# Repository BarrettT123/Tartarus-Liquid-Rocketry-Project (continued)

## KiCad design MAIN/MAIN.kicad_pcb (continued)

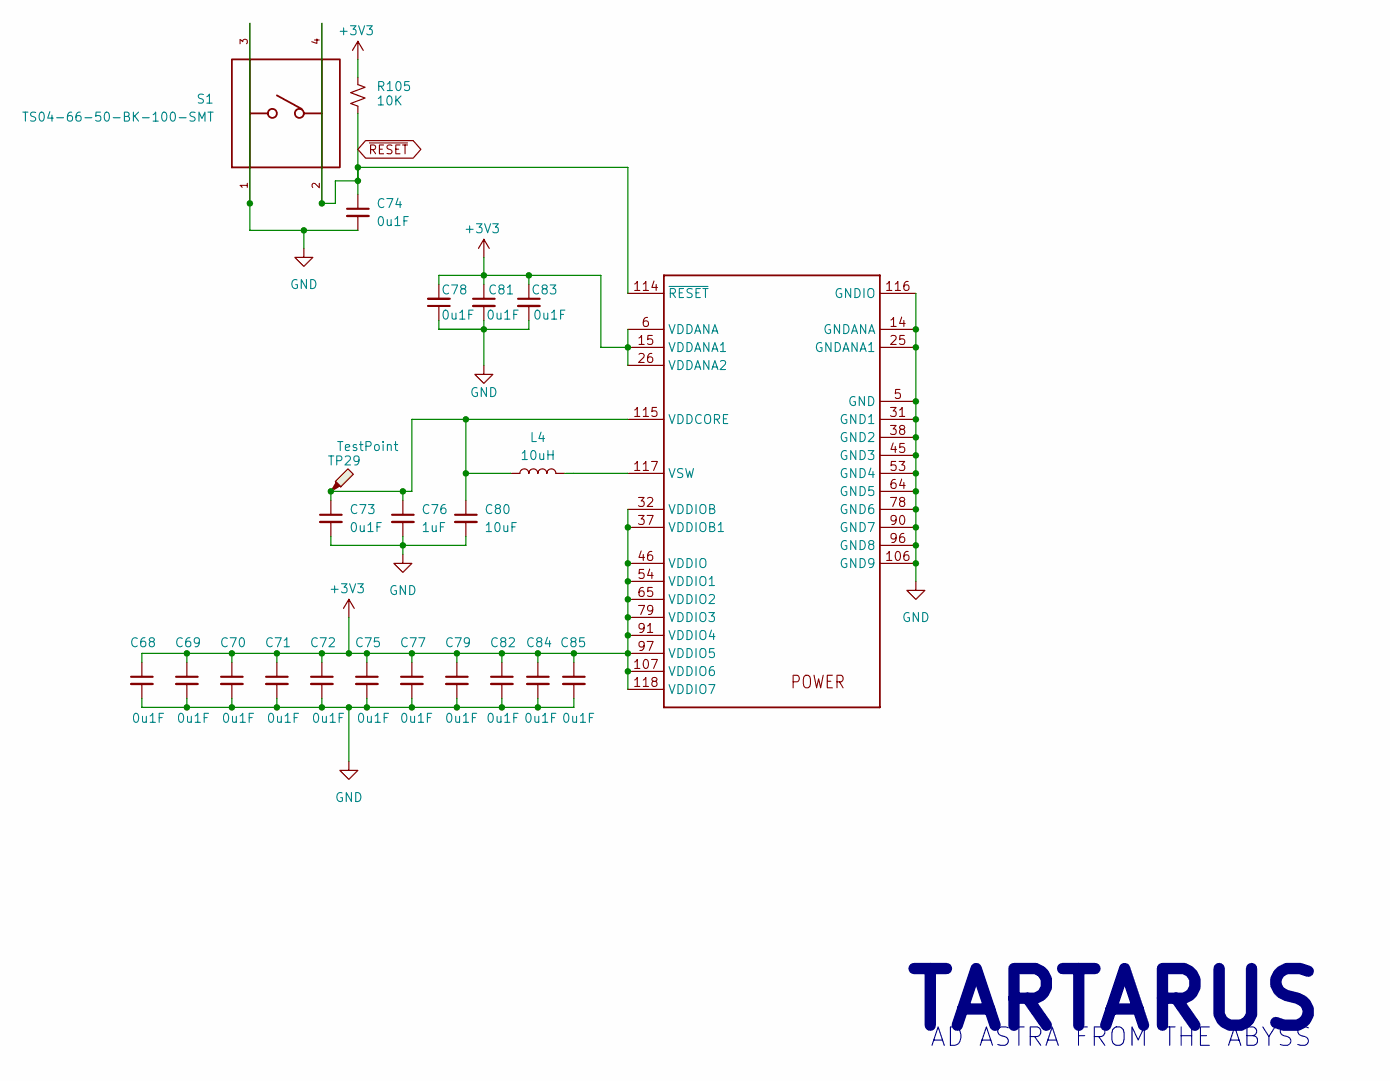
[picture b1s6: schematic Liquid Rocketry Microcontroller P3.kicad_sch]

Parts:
C68, C69, C70, C71, C72, C73, C74, C75, C77, C78, C79, C81, C82, C83, C84, C85: 0u1F; C_0603_1608Metric
C76: 1uF; C_0603_1608Metric
C80: 10uF; C_0603_1608Metric
L4: 10uH; L_1008_2520Metric
R105: 10K; R_0603_1608Metric
S1: TS04-66-50-BK-100-SMT; SW_TS04-66-50-BK-100-SMT; PARTREV 1.0
TP29: TestPoint; TestPoint_Pad_D1.0mm
U$1: SAMD51PXXA; SAMD51P20A-AF

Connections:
+3V3: C68.1, C69.1, C70.1, C71.1, C72.1, C75.1, C77.1, C78.2, C79.1, C81.1, C82.1, C83.1, C84.1, C85.1, R105.1, U$1.6 (VDDANA), U$1.15 (VDDANA1), U$1.26 (VDDANA2), U$1.32 (VDDIOB), U$1.37 (VDDIOB1), U$1.46 (VDDIO), U$1.54 (VDDIO1), U$1.65 (VDDIO2), U$1.79 (VDDIO3), U$1.91 (VDDIO4), U$1.97 (VDDIO5), U$1.107 (VDDIO6), U$1.118 (VDDIO7); also elsewhere on the board
GND: C68.2, C69.2, C70.2, C71.2, C72.2, C73.2, C74.2, C75.2, C76.2, C77.2, C78.1, C79.2, C80.2, C81.2, C82.2, C83.2, C84.2, C85.2, S1.1, S1.3, U$1.5 (GND), U$1.14 (GNDANA), U$1.25 (GNDANA1), U$1.31 (GND1), U$1.38 (GND2), U$1.45 (GND3), U$1.53 (GND4), U$1.64 (GND5), U$1.78 (GND6), U$1.90 (GND7), U$1.96 (GND8), U$1.106 (GND9), U$1.116 (GNDIO); also elsewhere on the board
unnamed: C73.1, C76.1, C80.1, L4.1, TP29.1, U$1.115 (VDDCORE)
unnamed: L4.2, U$1.117 (VSW)
~RESET: C74.1, R105.2, S1.2, S1.4, U$1.114 (~RESET); also elsewhere on the board

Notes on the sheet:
AD ASTRA FROM THE ABYSS
TARTARUS

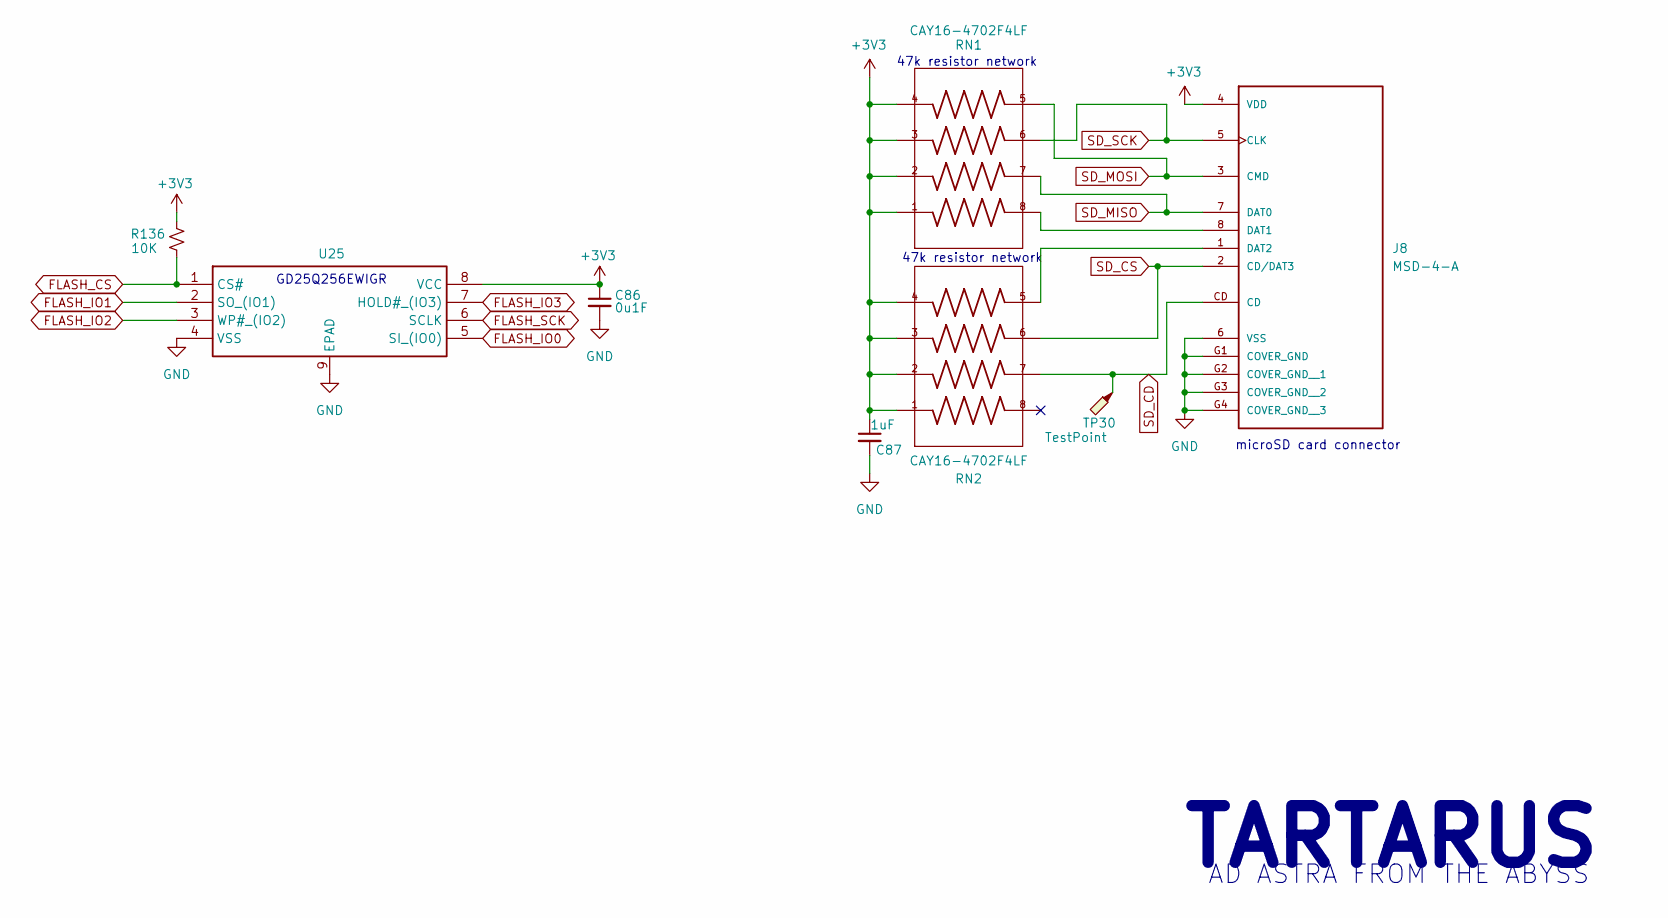
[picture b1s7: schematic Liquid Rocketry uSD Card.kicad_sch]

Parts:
C86: 0u1F; C_0603_1608Metric
C87: 1uF; C_0603_1608Metric
J8: MSD-4-A; CUI_MSD-4-A
R136: 10K; R_0603_1608Metric
RN1, RN2: CAY16-4702F4LF; CAY16_4702F4LF
TP30: TestPoint; TestPoint_Pad_D1.0mm
U25: GD25Q64ETIGR; WSON-8-1EP_6x5mm_P1.27mm_EP3.4x4mm; Mouser Part Number 363-GD25Q64ETIGR

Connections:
+3V3: C86.1, C87.1, J8.4 (VDD), R136.2, RN1.1, RN1.2, RN1.3, RN1.4, RN2.1, RN2.2, RN2.3, RN2.4, U25.8 (VCC); also elsewhere on the board
FLASH_CS: R136.1, U25.1 (CS#); also elsewhere on the board
FLASH_IO0: U25.5 (SI_(IO0)); also elsewhere on the board
FLASH_IO1: U25.2 (SO_(IO1)); also elsewhere on the board
FLASH_IO2: U25.3 (WP#_(IO2)); also elsewhere on the board
FLASH_IO3: U25.7 (HOLD#_(IO3)); also elsewhere on the board
FLASH_SCK: U25.6 (SCLK); also elsewhere on the board
GND: C86.2, C87.2, J8.6 (VSS), J8.G1 (COVER_GND), J8.G2 (COVER_GND__1), J8.G3 (COVER_GND__2), J8.G4 (COVER_GND__3), U25.4 (VSS), U25.9 (EPAD); also elsewhere on the board
unnamed: J8.8 (DAT1), RN1.8
unnamed: J8.1 (DAT2), RN2.5
SD_CD: J8.CD, RN2.7, TP30.1; also elsewhere on the board
SD_CS: J8.2 (CD/DAT3), RN2.6; also elsewhere on the board
SD_MISO: J8.7 (DAT0), RN1.7; also elsewhere on the board
SD_MOSI: J8.3 (CMD), RN1.5; also elsewhere on the board
SD_SCK: J8.5 (CLK), RN1.6; also elsewhere on the board

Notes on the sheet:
47k resistor network
AD ASTRA FROM THE ABYSS
microSD card connector
GD25Q256EWIGR
TARTARUS

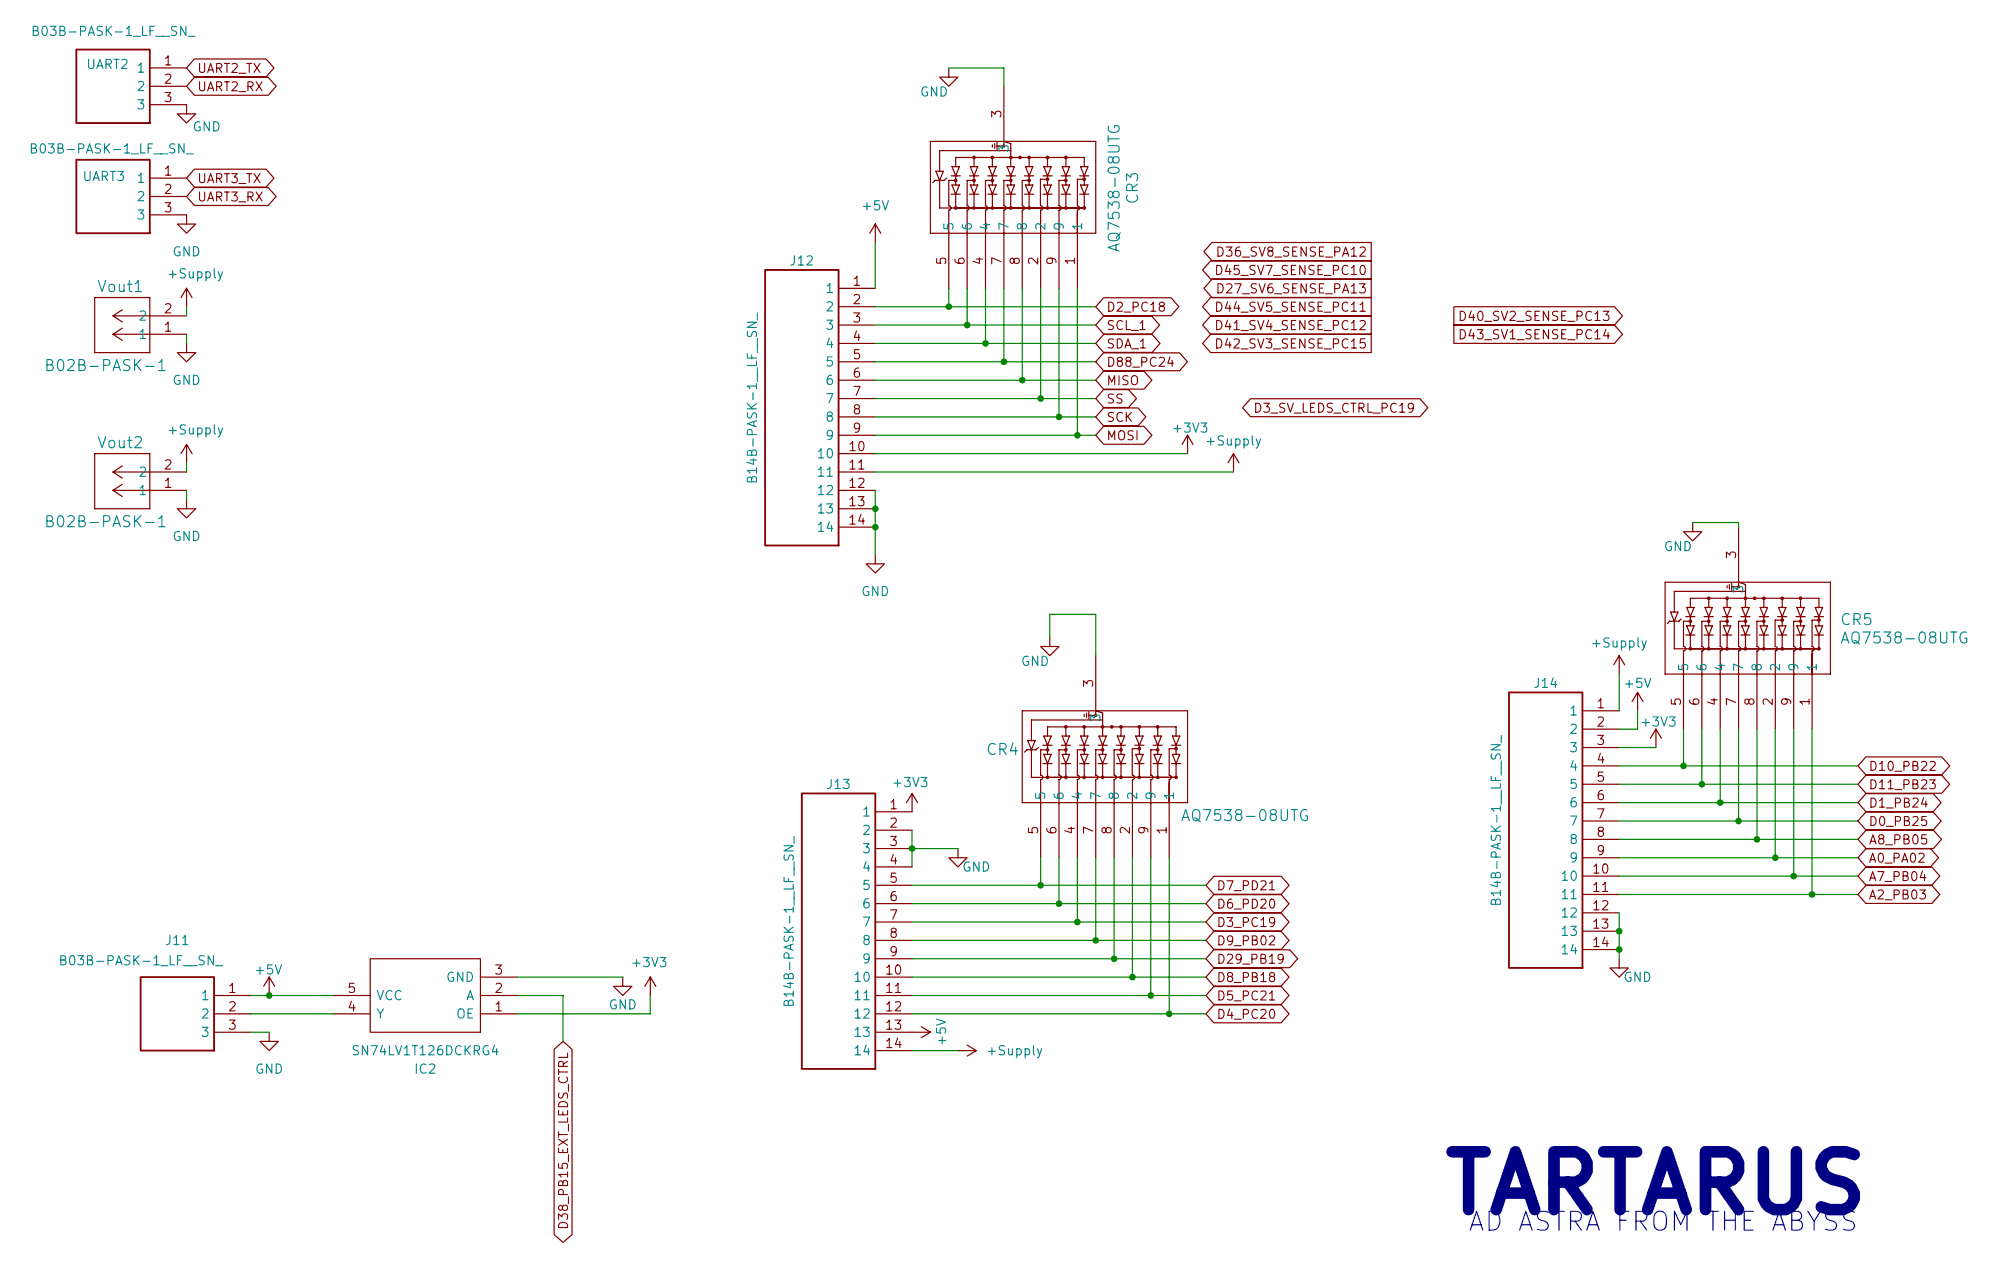
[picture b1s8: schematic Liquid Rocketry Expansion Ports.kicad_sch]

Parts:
CR3, CR4, CR5: AQ7538-08UTG; uDFN-9_3p8x1p0_LTF
IC2: SN74LV1T126DCKRG4; SOT65P210X110-5N; Mouser Part Number 595-74LV1T126DCKRG4
J11: B03B-PASK-1_LF__SN_; B03BPASK1LFSN; Mouser Part Number 306-B03BPASK1LFSN
J12, J13, J14: B14B-PASK-1__LF__SN_; B14BPASK1LFSN; Manufacturer_Part_Number B14B-PASK-1 (LF)(SN)
UART2, UART3: B03B-PASK-1_LF__SN_; B03BPASK1LFSN; Mouser Part Number 306-B03BPASK1LFSN
Vout1, Vout2: B02B-PASK-1; CONN_B02B-PASK-1_JST

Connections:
+3V3: IC2.1 (OE), J12.10, J13.1, J14.3; also elsewhere on the board
+5V: IC2.5 (VCC), J11.1, J12.1, J13.13, J14.2; also elsewhere on the board
+Supply: J12.11, J13.14, J14.1, Vout1.2, Vout2.2; also elsewhere on the board
A0_PA02: CR5.2, J14.9; also elsewhere on the board
A2_PB03: CR5.1, J14.11; also elsewhere on the board
A7_PB04: CR5.9, J14.10; also elsewhere on the board
A8_PB05: CR5.8, J14.8; also elsewhere on the board
D0_PB25: CR5.7, J14.7; also elsewhere on the board
D1_PB24: CR5.4, J14.6; also elsewhere on the board
D2_PC18: CR3.5, J12.2; also elsewhere on the board
D3_PC19: CR4.4, J13.7; also elsewhere on the board
D4_PC20: CR4.1, J13.12; also elsewhere on the board
D5_PC21: CR4.9, J13.11; also elsewhere on the board
D6_PD20: CR4.6, J13.6; also elsewhere on the board
D7_PD21: CR4.5, J13.5; also elsewhere on the board
D8_PB18: CR4.2, J13.10; also elsewhere on the board
D9_PB02: CR4.7, J13.8; also elsewhere on the board
D10_PB22: CR5.5, J14.4; also elsewhere on the board
D11_PB23: CR5.6, J14.5; also elsewhere on the board
D29_PB19: CR4.8, J13.9; also elsewhere on the board
D38_PB15_EXT_LEDS_CTRL: IC2.2 (A); also elsewhere on the board
D88_PC24: CR3.7, J12.5; also elsewhere on the board
GND: CR3.3, CR4.3, CR5.3, IC2.3 (GND), J11.3, J12.12, J12.13, J12.14, J13.2, J13.3, J13.4, J14.12, J14.13, J14.14, UART2.3, UART3.3, Vout1.1, Vout2.1; also elsewhere on the board
MISO: CR3.8, J12.6; also elsewhere on the board
MOSI: CR3.1, J12.9; also elsewhere on the board
unnamed: IC2.4 (Y), J11.2
SCK: CR3.9, J12.8; also elsewhere on the board
SCL_1: CR3.6, J12.3; also elsewhere on the board
SDA_1: CR3.4, J12.4; also elsewhere on the board
SS: CR3.2, J12.7; also elsewhere on the board
UART2_RX: UART2.2; also elsewhere on the board
UART2_TX: UART2.1; also elsewhere on the board
UART3_RX: UART3.2; also elsewhere on the board
UART3_TX: UART3.1; also elsewhere on the board

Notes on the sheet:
AD ASTRA FROM THE ABYSS
TARTARUS

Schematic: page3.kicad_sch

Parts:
C1, C88, C90: C_Small
C34, C36, C37: 0u1F; C_0603_1608Metric
C35: 470pF; C_0603_1608Metric
J4: B05B-PASK-1; CONN_B05B-PASK-1_JST
R19, R20: 51; R_0603_1608Metric
R153: ?; R_0603_1608Metric
TP9: TestPoint; TestPoint_Pad_D1.0mm
U6: NAU7802SGI; PARTREV 2.6
U26: INA333xxDRG; WSON-8-1EP_3x3mm_P0.5mm_EP1.45x2.4mm

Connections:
+3V3: C36.2, U6.15 (DVDD), U26.7 (V+); also elsewhere on the board
+Supply: J4.5; also elsewhere on the board
D12_LC_1_DRDY_PB01: TP9.1, U6.12 (DRDY); also elsewhere on the board
GND: C36.1, C37.1, J4.1, J4.2, U6.7 (REFN), U6.8 (AVSS), U6.9 (DVSS); also elsewhere on the board
unnamed: J4.3, R19.1
unnamed: J4.4, R20.1
unnamed: R153.1, U26.8 (Rg)
unnamed: R153.2, U26.1 (Rg)
unnamed: C37.2, U6.6 (VBG)
unnamed: C35.1, U6.4 (VIN2N)
unnamed: C35.2, U6.5 (VIN2P)
SCL_PB21: U6.13 (SCLK); also elsewhere on the board
SDA_PB20: U6.14 (SDIO); also elsewhere on the board

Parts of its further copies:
C38, C40, C41: 0u1F; C_0603_1608Metric
C39: 470pF; C_0603_1608Metric
J5: B05B-PASK-1; CONN_B05B-PASK-1_JST
R21, R22: 51; R_0603_1608Metric
TP10: TestPoint; TestPoint_Pad_D1.0mm
U7: NAU7802SGI; PARTREV 2.6

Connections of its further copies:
+3V3: C40.2, U7.15 (DVDD); also elsewhere on the board
+Supply: J5.5; also elsewhere on the board
D13_LC_2_DRDY__PB00: TP10.1, U7.12 (DRDY); also elsewhere on the board
GND: C40.1, C41.1, J5.1, J5.2, U7.7 (REFN), U7.8 (AVSS), U7.9 (DVSS); also elsewhere on the board
unnamed: J5.3, R21.1
unnamed: J5.4, R22.1
unnamed: C41.2, U7.6 (VBG)
unnamed: C38.1, R22.2, U7.2 (VIN1N)
unnamed: C38.2, R21.2, U7.3 (VIN1P)
unnamed: C39.1, U7.4 (VIN2N)
unnamed: C39.2, U7.5 (VIN2P)
SCL_PB21: U7.13 (SCLK); also elsewhere on the board
SDA_PB20: U7.14 (SDIO); also elsewhere on the board

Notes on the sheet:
TARTARUS
AD ASTRA FROM THE ABYSS

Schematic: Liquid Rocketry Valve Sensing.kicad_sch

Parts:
CR2: AQ7538-08UTG; uDFN-9_3p8x1p0_LTF
J9, J10: B07B-PASK-1; CONN_B07B-PASK-1_JST
R137, R138, R139, R140, R141, R142, R143, R144: 90K9; R_0603_1608Metric
R145, R146, R147, R148, R149, R151, R152: 10K; R_0603_1608Metric
R150: 1K; R_0603_1608Metric

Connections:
+3V3: J10.7; also elsewhere on the board
+5V: J9.1; also elsewhere on the board
D27_SV6_SENSE_PA13: CR2.2, R142.2, R150.1; also elsewhere on the board
D28_SV_LEDS_CTRL_PA14: J9.2; also elsewhere on the board
D36_SV8_SENSE_PA12: CR2.1, R144.2, R152.1; also elsewhere on the board
D40_SV2_SENSE_PC13: CR2.6, R138.2, R146.1; also elsewhere on the board
D41_SV4_SENSE_PC12: CR2.7, R140.2, R148.1; also elsewhere on the board
D42_SV3_SENSE_PC15: CR2.4, R139.2, R147.1; also elsewhere on the board
D43_SV1_SENSE_PC14: CR2.5, R137.2, R145.1; also elsewhere on the board
D44_SV5_SENSE_PC11: CR2.8, R141.2, R149.1; also elsewhere on the board
D45_SV7_SENSE_PC10: CR2.9, R143.2, R151.1; also elsewhere on the board
GND: CR2.3, J10.4, J10.5, J10.6, R145.2, R146.2, R147.2, R148.2, R149.2, R150.2, R151.2, R152.2; also elsewhere on the board
unnamed: J9.3, R137.1
unnamed: J9.4, R138.1
unnamed: J9.5, R139.1
unnamed: J9.6, R140.1
unnamed: J9.7, R141.1
unnamed: J10.1, R142.1
unnamed: J10.2, R143.1
unnamed: J10.3, R144.1

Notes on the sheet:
AD ASTRA FROM THE ABYSS
TARTARUS

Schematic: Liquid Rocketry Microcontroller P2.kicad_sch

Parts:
D14, D15: LEDA; LED_0603_1608Metric
R106, R107: 2k2; R_0603_1608Metric
R108, R109: 1K; R_0603_1608Metric
U$1: SAMD51PXXA; SAMD51P20A-AF

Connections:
+3V3: R106.1, R107.1; also elsewhere on the board
/Microcontroller Page 2 (PC_PD)/A1_TC_2_FLT_DET_PA05: U$1.29 (PC06/I6/SERCOM6.2/SDHC0.SDCD); also elsewhere on the board
/Microcontroller Page 2 (PC_PD)/A13_TC_1_FLT_DET_PA04: U$1.30 (PC07/I9/SERCOM6.3/SDHC0.SDWP); also elsewhere on the board
/Microcontroller Page 2 (PC_PD)/A14_TC_3_FLT_DET_PA06: U$1.28 (PC05/I5/SERCOM6.0/TCC0.0); also elsewhere on the board
/Microcontroller Page 2 (PC_PD)/A15_TC_4_FLT_DET_PA07: U$1.27 (PC04/I4/SERCOM6.0/TCC0.0); also elsewhere on the board
A03_PT_1_PC00: U$1.3 (PC00/I1/ADC1.10); also elsewhere on the board
A04_PT_2_PC01: U$1.4 (PC01/I1/ADC1.11); also elsewhere on the board
A05_PT_3_PC02: U$1.7 (PC02/I2/ADC1.4); also elsewhere on the board
A06_PT_4_PC03: U$1.8 (PC03/I3/ADC1.5); also elsewhere on the board
D2_PC18: U$1.72 (PC18/I2/SERCOM6.2+0.2/TCC0.2/QDI.2); also elsewhere on the board
D3_PC19: U$1.73 (PC19/I3/SERCOM6+0.3/TCC0.3); also elsewhere on the board
D4_PC20: U$1.74 (PC20/I4/TCC0.4/SDHC1.SDCD); also elsewhere on the board
D5_PC21: U$1.75 (PC21/I5/TCC0.5/SDHC1.SDWP); also elsewhere on the board
D6_PD20: U$1.80 (PD20/I10/SERCOM1+3.2/TCC1.0/SDHC1.SDCD); also elsewhere on the board
D7_PD21: U$1.81 (PD21/I11/SERCOM1+3.3/TCC1.1/SDHC1.SDWP); also elsewhere on the board
D27_SV6_SENSE_PA13: U$1.56 (PC12/I12/SERCOM7.0+6.1/TCC0.2+1.6); also elsewhere on the board
D36_SV8_SENSE_PA12: U$1.52 (PC10/I10/SERCOM6.2+7.2/TCC0.0+1.4); also elsewhere on the board
D41_SV4_SENSE_PC12: U$1.58 (PC14/I14/SERCOM7+6.2/TCC0.4+1.0); also elsewhere on the board
D42_SV3_SENSE_PC15: U$1.59 (PC15/I15/SERCOM7+6.3/TCC0.5+1.1); also elsewhere on the board
D44_SV5_SENSE_PC11: U$1.57 (PC13/I13/SERCOM7.1+6.0/TCC0.3+1.7); also elsewhere on the board
D45_SV7_SENSE_PC10: U$1.55 (PC11/I11/SERCOM6+7.3/TCC0.1+1.5); also elsewhere on the board
D88_PC24: U$1.108 (PC24/I8/SERCOM0+2.2/TRACEDATA.3); also elsewhere on the board
GND: R108.1, R109.2; also elsewhere on the board
MISO: U$1.50 (PD11/I6/SERCOM7+6.3/TCC0.4); also elsewhere on the board
MOSI: U$1.47 (PD08/I3/SERCOM7.0+6.1/TCC0.1); also elsewhere on the board
unnamed: D14.1 (K), R108.2
unnamed: D15.1 (K), R109.1
RXLED: D14.2 (A), U$1.124 (PC31/I15/AIN1.13)
SCK: U$1.48 (PD09/I4/SERCOM7.1+6.0/TCC0.2); also elsewhere on the board
SCL_1: R107.2, U$1.71 (PC17/I1/SERCOM6.1+0.0/TCC0.1/QDI.1); also elsewhere on the board
SDA_1: R106.2, U$1.70 (PC16/I0/SERCOM6.0+0.1/TCC0/QDI.0); also elsewhere on the board
SS: U$1.49 (PD10/I5/SERCOM7+6.2/TCC0.3); also elsewhere on the board
TXLED: D15.2 (A), U$1.123 (PC30/I14/AIN1.12)
UART2_RX: U$1.77 (PC23/I7/SERCOM1.1+3.0/TCC0.7); also elsewhere on the board
UART2_TX: U$1.76 (PC22/I6/SERCOM1.0+3.1/TCC0.6); also elsewhere on the board

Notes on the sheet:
AD ASTRA FROM THE ABYSS
TARTARUS

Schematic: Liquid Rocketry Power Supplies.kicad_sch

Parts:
C2, C5: 680uF; CAP_PY-13x20_KEM_A759PY687M1HAAE026
C4, C6, C16: 0u1; C_0603_1608Metric
C7, C9: 10uF; C_0603_1608Metric
C8: 2u2F; C_0603_1608Metric
C10: 5600pF; C_0603_1608Metric
C11, C15, C20, C25, C27: 4u7F; C_0603_1608Metric
C12, C13: 100nF; C_0603_1608Metric
C14, C17, C18, C19, C21, C22, C23, C24, C26, C28, C29, C31: 22uF; C_0805_2012Metric
C30: 100pF; C_0603_1608Metric
C32: 1uF; C_0603_1608Metric
C33: 100uF; WCAP-PTHR_10X12.5_DXL_870055675009
D1, D2, D3, D4, D5: LEDG; LED_0603_1608Metric
J2, J3: 2601-3102; Molex_2x2_1724480004
L1: 10uH; SRP7028A3R3M
L2: 4u7H; 74438357047
L3: 8u2H; IND_CB_DRA127
Q1: SI7252DP-T1-GE3; TRANS_SI7942DP-T1-E3; PARTREV C
R1: 5M62; R_0603_1608Metric
R2: 184K; R_0603_1608Metric
R3: 115K; R_0603_1608Metric
R4, R5: 510K; R_0603_1608Metric
R6, R9, R10, R11, R12, R13: 100R; R_0603_1608Metric
R7, R8, R14, R15: 4K; R_0603_1608Metric
R16: 51K1; R_0603_1608Metric
R17: 100K; R_0603_1608Metric
R18: 15K4; R_0603_1608Metric
TP1, TP2, TP3, TP4, TP6, TP7, TP8: TestPoint; TestPoint_Pad_D1.0mm
U1: LTC4367HDD-TRPBF; DD_8_ADI
U2: REF3133AIDBZR; LT1460KCS3_3_3_TRMPBF
U3: MAX17634BATP+; MAX17634BATP
U4: AP63203WU-7; AP63203WU-7_DIO
U5: AP63201WU-7; AP63203WU-7_DIO

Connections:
+3V3: C18.1, C22.1, C27.1, C32.1, D1.2 (A), L2.1, U4.1 (FB); also elsewhere on the board
+5V: C4.1, C24.1, C26.1, C28.1, C29.1, C31.1, C33.1, D3.2 (A), L3.2, U2.1 (IN), U3.9 (FB), U3.12 (EXTVCC); also elsewhere on the board
+6V: C14.1, C17.1, C19.1, C21.1, C23.1, C25.1, C30.1, D4.2 (A), L1.1, R17.1; also elsewhere on the board
+Relay_External: C2.1, D5.2 (A), J2.2 (1_2), J2.4 (2_2), TP3.1; also elsewhere on the board
+Supply: C5.1, C7.1, C9.1, C11.1, C15.1, C20.1, D2.2 (A), Q1.5_6, U1.7 (VOUT), U3.2 (IN), U3.3 (IN), U3.4 (EN/UVLO), U3.14 (IN), U4.2 (EN), U4.3 (VIN), U5.2 (EN), U5.3 (VIN); also elsewhere on the board
AREF: C6.1, TP8.1, U2.2 (OUT); also elsewhere on the board
GND: C2.2, C4.2, C5.2, C6.2, C7.2, C8.2, C9.2, C10.2, C11.2, C14.2, C15.2, C17.2, C18.2, C19.2, C20.2, C21.2, C22.2, C23.2, C24.2, C25.2, C26.2, C27.2, C28.2, C29.2, C31.2, C32.2, C33.2, J2.1 (1_1), J2.3 (2_1), J3.1 (1_1), J3.3 (2_1), R3.2, R5.2, R6.1, R7.2, R8.2, R10.1, R13.1, R14.2, R15.2, R16.1, R18.2, U1.4 (GND), U1.9 (EPAD), U2.3 (GND), U3.1 (PGND), U3.7 (SGND), U3.11 (MODE/SYNC), U3.15 (PGND), U3.21 (EPAD), U4.4 (GND), U5.4 (GND); also elsewhere on the board
unnamed: C16.1, L3.1, U3.17 (LX), U3.18 (LX), U3.19 (LX)
unnamed: D1.1 (K), R6.2
unnamed: D2.1 (K), R7.1, R8.1
unnamed: D3.1 (K), R9.2
unnamed: D4.1 (K), R11.2
unnamed: D5.1 (K), R14.1, R15.1
unnamed: J3.2 (1_2), J3.4 (2_2), Q1.7_8, R1.1, R4.1, TP4.1, U1.1 (VIN)
unnamed: Q1.1, Q1.3
unnamed: R9.1, R10.2
unnamed: R11.1, R12.2
unnamed: R12.1, R13.2
unnamed: Q1.2, Q1.4, TP6.1, U1.8 (GATE)
unnamed: R2.2, R3.1, TP2.1, U1.3 (OV)
unnamed: R4.2, R5.1, TP7.1, U1.5 (SHDN)
unnamed: R1.2, R2.1, TP1.1, U1.2 (UV)
unnamed: C16.2, U3.20 (BST)
unnamed: C8.1, U3.6 (INTVCC)
unnamed: R16.2, U3.10 (RT)
unnamed: C10.1, U3.8 (SS)
unnamed: C13.1, U4.6 (BST)
unnamed: C13.2, L2.2, U4.5 (SW)
unnamed: C12.1, U5.6 (BST)
unnamed: C30.2, R17.2, R18.1, U5.1 (FB)
unnamed: C12.2, L1.2, U5.5 (SW)

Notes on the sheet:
TARTARUS
Main Power Connection Functional voltage range: 10-26V Absolute maximum input voltage: 100 V DC
Molex 1724480004
WARNING! EXCEEDING 100V INPUT WILL CAUSE PERMANENT DAMAGE TO THE SYSTEM
DC POWER ONLY!
SO-8 PowerPAK dual N-channel MOSFETs
AD ASTRA FROM THE ABYSS

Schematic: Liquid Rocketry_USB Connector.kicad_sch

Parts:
J7: USB4085-GF-A_REVB; GCT_USB4085-GF-A_REVB
R134, R135: 5K1; R_0603_1608Metric
U24: USBLC6-2SC6; USBLC_6

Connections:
/Microcontroller Page 1 (PA_PB)/USB Connector/USB_D+: U24.6; also elsewhere on the board
/Microcontroller Page 1 (PA_PB)/USB Connector/USB_D-: U24.4; also elsewhere on the board
GND: J7.A1 (GND), J7.A12 (GND__1), J7.B1 (GND__2), J7.B12 (GND__3), J7.S1 (SHELL), J7.S2 (SHELL__1), J7.S3 (SHELL__2), J7.S4 (SHELL__3), R134.1, R135.2, U24.2; also elsewhere on the board
unnamed: J7.A5 (CC1), R134.2
unnamed: J7.B5 (CC2), R135.1
USBDN: J7.A7 (DN1), J7.B7 (DN2), U24.3
USBDP: J7.A6 (DP1), J7.B6 (DP2), U24.1
USB_VBUS: J7.A4 (VBUS), J7.A9 (VBUS__1), J7.B4 (VBUS__2), J7.B9 (VBUS__3), U24.5

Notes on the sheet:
TARTARUS
AD ASTRA FROM THE ABYSS

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
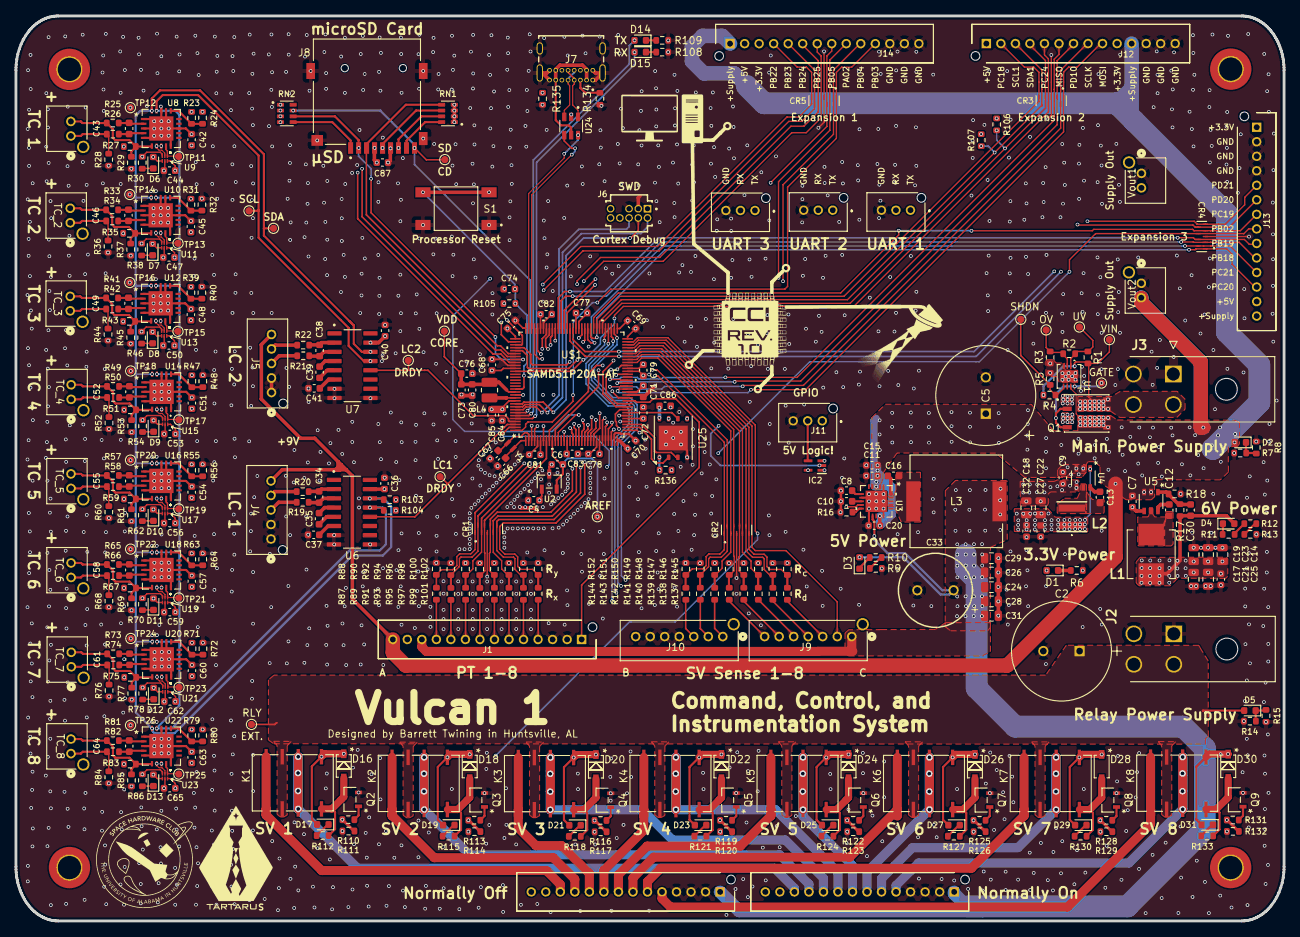
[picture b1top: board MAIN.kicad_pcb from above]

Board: 6 copper layers, 174.6 x 124.6 mm, 387 parts (0 on the bottom side), 268 nets.

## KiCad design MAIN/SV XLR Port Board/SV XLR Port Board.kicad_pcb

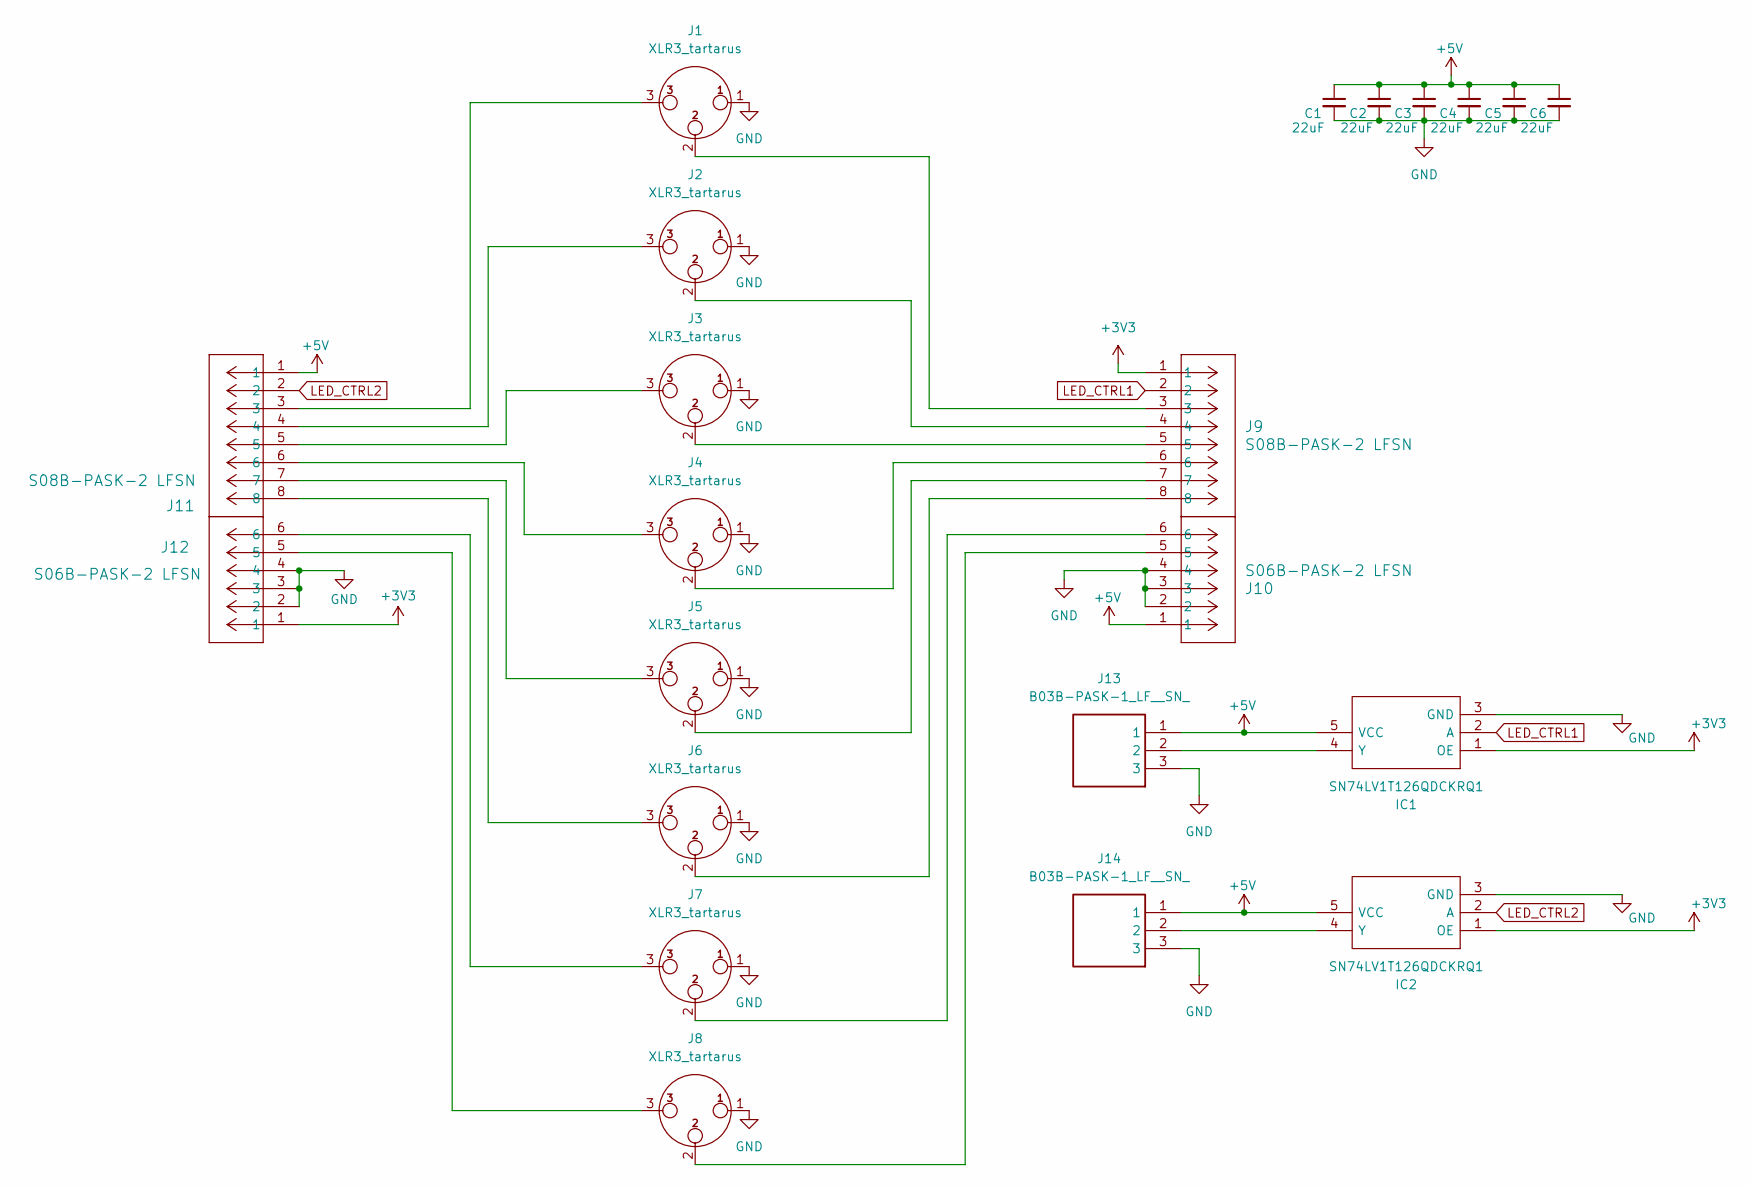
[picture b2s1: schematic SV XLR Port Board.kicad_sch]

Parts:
C1, C2, C3, C4, C5, C6: 22uF; C_0805_2012Metric
IC1, IC2: SN74LV1T126QDCKRQ1; SOT65P210X110-5N; Mouser Part Number 595-74LV1T126DCKRG4
J1, J2, J3, J4, J5, J6, J7, J8: XLR3_tartarus; AC3FAH1-AU-PRE (3)
J9, J11: S08B-PASK-2 LFSN; CONN_S08B-PASK-2_JST
J10, J12: S06B-PASK-2 LFSN; CONN6_S06B-PASK-2 LFSN_JST
J13, J14: B03B-PASK-1_LF__SN_; B03BPASK1LFSN; Mouser Part Number 306-B03BPASK1LFSN

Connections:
+3V3: IC1.1 (OE), IC2.1 (OE), J9.1, J12.1
+5V: C1.1, C2.1, C3.1, C4.1, C5.1, C6.1, IC1.5 (VCC), IC2.5 (VCC), J10.1, J11.1, J13.1, J14.1
GND: C1.2, C2.2, C3.2, C4.2, C5.2, C6.2, IC1.3 (GND), IC2.3 (GND), J1.1, J2.1, J3.1, J4.1, J5.1, J6.1, J7.1, J8.1, J10.2, J10.3, J10.4, J12.2, J12.3, J12.4, J13.3, J14.3
LED_CTRL1: IC1.2 (A), J9.2
LED_CTRL2: IC2.2 (A), J11.2
unnamed: IC1.4 (Y), J13.2
unnamed: IC2.4 (Y), J14.2
unnamed: J1.2, J9.3
unnamed: J1.3, J11.3
unnamed: J2.2, J9.4
unnamed: J3.2, J9.5
unnamed: J4.2, J9.6
unnamed: J5.2, J9.7
unnamed: J6.2, J9.8
unnamed: J8.2, J10.5
unnamed: J7.2, J10.6
unnamed: J2.3, J11.4
unnamed: J3.3, J11.5
unnamed: J4.3, J11.6
unnamed: J5.3, J11.7
unnamed: J6.3, J11.8
unnamed: J8.3, J12.5
unnamed: J7.3, J12.6

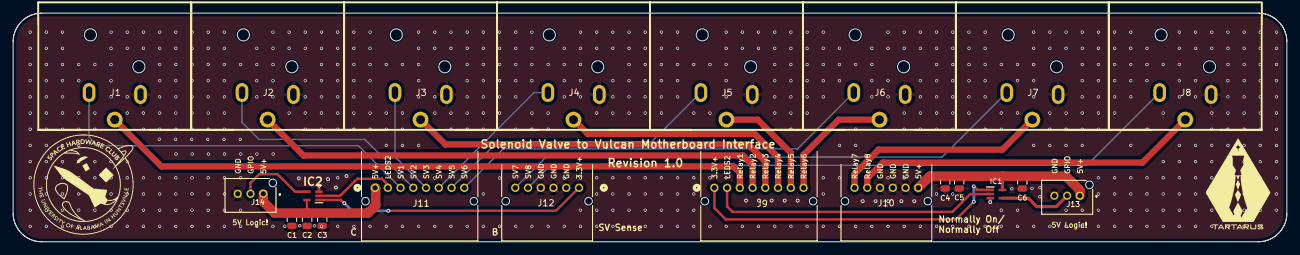
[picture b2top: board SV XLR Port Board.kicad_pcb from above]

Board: 2 copper layers, 199.9 x 35.9 mm, 22 parts (0 on the bottom side), 23 nets.

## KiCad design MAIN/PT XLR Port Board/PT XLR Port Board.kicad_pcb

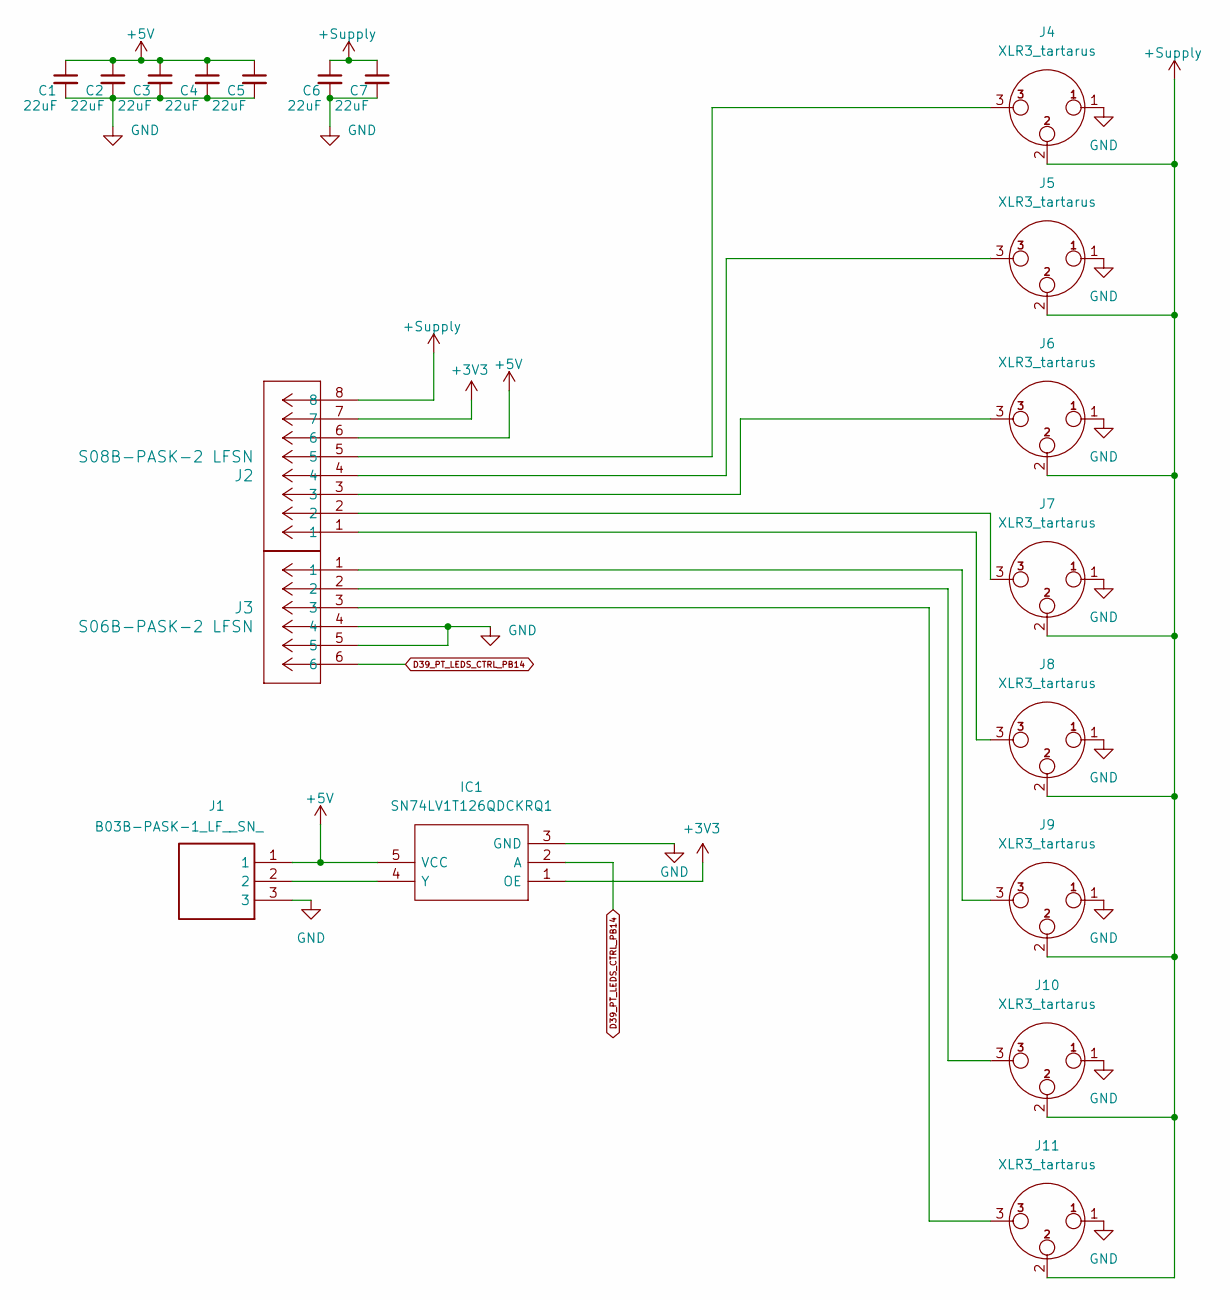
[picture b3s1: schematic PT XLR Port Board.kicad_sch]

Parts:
C1, C2, C3, C4, C5, C6, C7: 22uF; C_0805_2012Metric
IC1: SN74LV1T126QDCKRQ1; SOT65P210X110-5N; Mouser Part Number 595-74LV1T126DCKRG4
J1: B03B-PASK-1_LF__SN_; B03BPASK1LFSN; Mouser Part Number 306-B03BPASK1LFSN
J2: S08B-PASK-2 LFSN; CONN_S08B-PASK-2_JST
J3: S06B-PASK-2 LFSN; CONN6_S06B-PASK-2 LFSN_JST
J4, J5, J6, J7, J8, J9, J10, J11: XLR3_tartarus; AC3FAH1-AU-PRE (3)

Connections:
+3V3: IC1.1 (OE), J2.7
+5V: C1.1, C2.1, C3.1, C4.1, C5.1, IC1.5 (VCC), J1.1, J2.6
+Supply: C6.1, C7.1, J2.8, J4.2, J5.2, J6.2, J7.2, J8.2, J9.2, J10.2, J11.2
D39_PT_LEDS_CTRL_PB14: IC1.2 (A), J3.6
GND: C1.2, C2.2, C3.2, C4.2, C5.2, C6.2, C7.2, IC1.3 (GND), J1.3, J3.4, J3.5, J4.1, J5.1, J6.1, J7.1, J8.1, J9.1, J10.1, J11.1
unnamed: IC1.4 (Y), J1.2
unnamed: J2.1, J8.3
unnamed: J2.2, J7.3
unnamed: J2.3, J6.3
unnamed: J2.4, J5.3
unnamed: J2.5, J4.3
unnamed: J3.1, J9.3
unnamed: J3.2, J10.3
unnamed: J3.3, J11.3

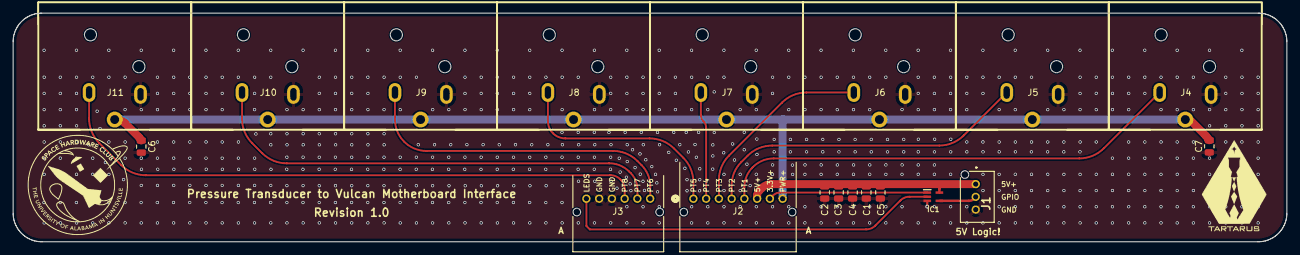
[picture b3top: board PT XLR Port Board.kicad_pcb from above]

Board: 2 copper layers, 199.9 x 35.9 mm, 19 parts (0 on the bottom side), 14 nets.

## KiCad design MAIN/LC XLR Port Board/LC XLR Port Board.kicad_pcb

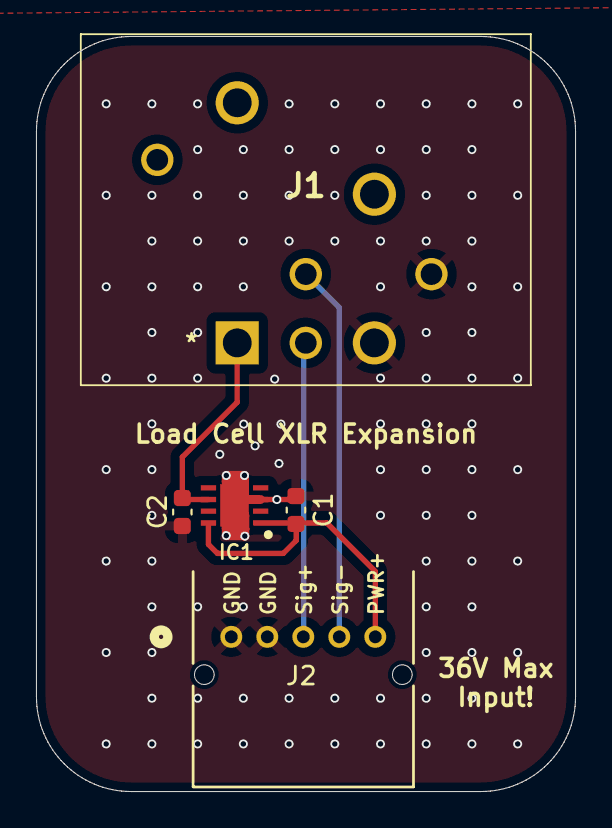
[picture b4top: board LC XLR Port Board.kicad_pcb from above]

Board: 2 copper layers, 29.9 x 41.9 mm, 5 parts (0 on the bottom side), 5 nets.

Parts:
C1, C2: 10uF; C_0603_1608Metric
IC1: RTQ2569-90GQW-QA; SON65P300X300X80-9N
J1: IO-XLR5-F-EH; AC5FAHAUB
J2: S05B-PASK-2LFSN; CONN_S05B-PASK-2_JST

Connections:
GND: C1.2, C2.2, IC1.3 (GND), IC1.9 (GND), J1.4, J1.5, J2.1, J2.2
unnamed: C1.1, IC1.1 (VCC), IC1.8 (EN), J2.5
unnamed: C2.1, IC1.6 (VOUT), J1.1
unnamed: J1.2, J2.4
unnamed: J1.3, J2.3

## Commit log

2025-11-15 Test
    Test
2025-11-15 changed
    changed
2025-11-15 update cap
2025-11-15 stuff
2025-11-15 serrtse
2025-11-17 fdggsfdfdgsfera
2025-12-12 sdfghjkl;
